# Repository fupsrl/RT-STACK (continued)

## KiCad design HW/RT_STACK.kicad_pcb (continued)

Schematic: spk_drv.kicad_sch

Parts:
C55: 100nF; C_0402_1005Metric
C56, C57: 220nF; C_0402_1005Metric
D25, D26, D27, D28: SK520B; D_SMB; LCSC C139681
Q19, Q20: RGPR30BM40; TO-252-2
R67, R68, R69, R70: 10; R_0402_1005Metric
U34: TC4427xOA; SOIC-8_3.9x4.9mm_P1.27mm; JLC C640788

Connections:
+5V: C55.1, U34.6 (VDD); also elsewhere on the board
+BATT: D25.1 (K), D27.1 (K); also elsewhere on the board
GND: C55.2, D26.2 (A), D28.2 (A), Q19.3 (E), Q20.3 (E), R69.1, R70.1, U34.3 (GND); also elsewhere on the board
IGN1: U34.2 (IN_A); also elsewhere on the board
IGN2: U34.4 (IN_B); also elsewhere on the board
unnamed: C56.2, R69.2
unnamed: C57.2, R70.2
unnamed: Q19.1 (G), R67.1
unnamed: Q20.1 (G), R68.1
unnamed: R67.2, U34.7 (OUT_A)
unnamed: R68.2, U34.5 (OUT_B)
SPK1: C57.1, D27.2 (A), D28.1 (K), Q20.2 (C); also elsewhere on the board
SPK2: C56.1, D25.2 (A), D26.1 (K), Q19.2 (C); also elsewhere on the board

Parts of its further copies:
C58, C61, C64, C67, C70: 100nF; C_0402_1005Metric
C59, C60, C62, C63, C65, C66, C68, C69, C71, C72: 220nF; C_0402_1005Metric
D29, D30, D31, D32, D33, D34, D35, D36, D37, D38, D39, D40, D41, D42, D43, D44, D45, D46, D47, D48: SK520B; D_SMB; LCSC C139681
Q21, Q22, Q23, Q24, Q25, Q26, Q27, Q28, Q29, Q30: RGPR30BM40; TO-252-2
R71, R72, R73, R74, R75, R76, R77, R78, R79, R80, R81, R82, R83, R84, R85, R86, R87, R88, R89, R90: 10; R_0402_1005Metric
U35, U36, U37, U38, U39: TC4427xOA; SOIC-8_3.9x4.9mm_P1.27mm; JLC C640788

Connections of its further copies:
+5V: C58.1, C61.1, C64.1, C67.1, C70.1, U35.6 (VDD), U36.6 (VDD), U37.6 (VDD), U38.6 (VDD), U39.6 (VDD); also elsewhere on the board
+BATT: D29.1 (K), D31.1 (K), D33.1 (K), D35.1 (K), D37.1 (K), D39.1 (K), D41.1 (K), D43.1 (K), D45.1 (K), D47.1 (K); also elsewhere on the board
GND: C58.2, C61.2, C64.2, C67.2, C70.2, D30.2 (A), D32.2 (A), D34.2 (A), D36.2 (A), D38.2 (A), D40.2 (A), D42.2 (A), D44.2 (A), D46.2 (A), D48.2 (A), Q21.3 (E), Q22.3 (E), Q23.3 (E), Q24.3 (E), Q25.3 (E), Q26.3 (E), Q27.3 (E), Q28.3 (E), Q29.3 (E), Q30.3 (E), R73.1, R74.1, R77.1, R78.1, R81.1, R82.1, R85.1, R86.1, R89.1, R90.1, U35.3 (GND), U36.3 (GND), U37.3 (GND), U38.3 (GND), U39.3 (GND); also elsewhere on the board
IGN3: U35.2 (IN_A); also elsewhere on the board
IGN4: U35.4 (IN_B); also elsewhere on the board
IGN5: U36.2 (IN_A); also elsewhere on the board
IGN6: U36.4 (IN_B); also elsewhere on the board
IGN7: U37.2 (IN_A); also elsewhere on the board
IGN8: U37.4 (IN_B); also elsewhere on the board
IGN9: U38.2 (IN_A); also elsewhere on the board
IGN10: U38.4 (IN_B); also elsewhere on the board
IGN11: U39.2 (IN_A); also elsewhere on the board
IGN12: U39.4 (IN_B); also elsewhere on the board
unnamed: C59.2, R73.2
unnamed: C60.2, R74.2
unnamed: C62.2, R77.2
unnamed: C63.2, R78.2
unnamed: C65.2, R81.2
unnamed: C66.2, R82.2
unnamed: C68.2, R85.2
unnamed: C69.2, R86.2
unnamed: C71.2, R89.2
unnamed: C72.2, R90.2
unnamed: Q21.1 (G), R71.1
unnamed: Q22.1 (G), R72.1
unnamed: Q23.1 (G), R75.1
unnamed: Q24.1 (G), R76.1
unnamed: Q25.1 (G), R79.1
unnamed: Q26.1 (G), R80.1
unnamed: Q27.1 (G), R83.1
unnamed: Q28.1 (G), R84.1
unnamed: Q29.1 (G), R87.1
unnamed: Q30.1 (G), R88.1
unnamed: R71.2, U35.7 (OUT_A)
unnamed: R72.2, U35.5 (OUT_B)
unnamed: R75.2, U36.7 (OUT_A)
unnamed: R76.2, U36.5 (OUT_B)
unnamed: R79.2, U37.7 (OUT_A)
unnamed: R80.2, U37.5 (OUT_B)
unnamed: R83.2, U38.7 (OUT_A)
unnamed: R84.2, U38.5 (OUT_B)
unnamed: R87.2, U39.7 (OUT_A)
unnamed: R88.2, U39.5 (OUT_B)
SPK3: C60.1, D31.2 (A), D32.1 (K), Q22.2 (C); also elsewhere on the board
SPK4: C59.1, D29.2 (A), D30.1 (K), Q21.2 (C); also elsewhere on the board
SPK5: C63.1, D35.2 (A), D36.1 (K), Q24.2 (C); also elsewhere on the board
SPK6: C62.1, D33.2 (A), D34.1 (K), Q23.2 (C); also elsewhere on the board
SPK7: C66.1, D39.2 (A), D40.1 (K), Q26.2 (C); also elsewhere on the board
SPK8: C65.1, D37.2 (A), D38.1 (K), Q25.2 (C); also elsewhere on the board
SPK9: C69.1, D43.2 (A), D44.1 (K), Q28.2 (C); also elsewhere on the board
SPK10: C68.1, D41.2 (A), D42.1 (K), Q27.2 (C); also elsewhere on the board
SPK11: C72.1, D47.2 (A), D48.1 (K), Q30.2 (C); also elsewhere on the board
SPK12: C71.1, D45.2 (A), D46.1 (K), Q29.2 (C); also elsewhere on the board

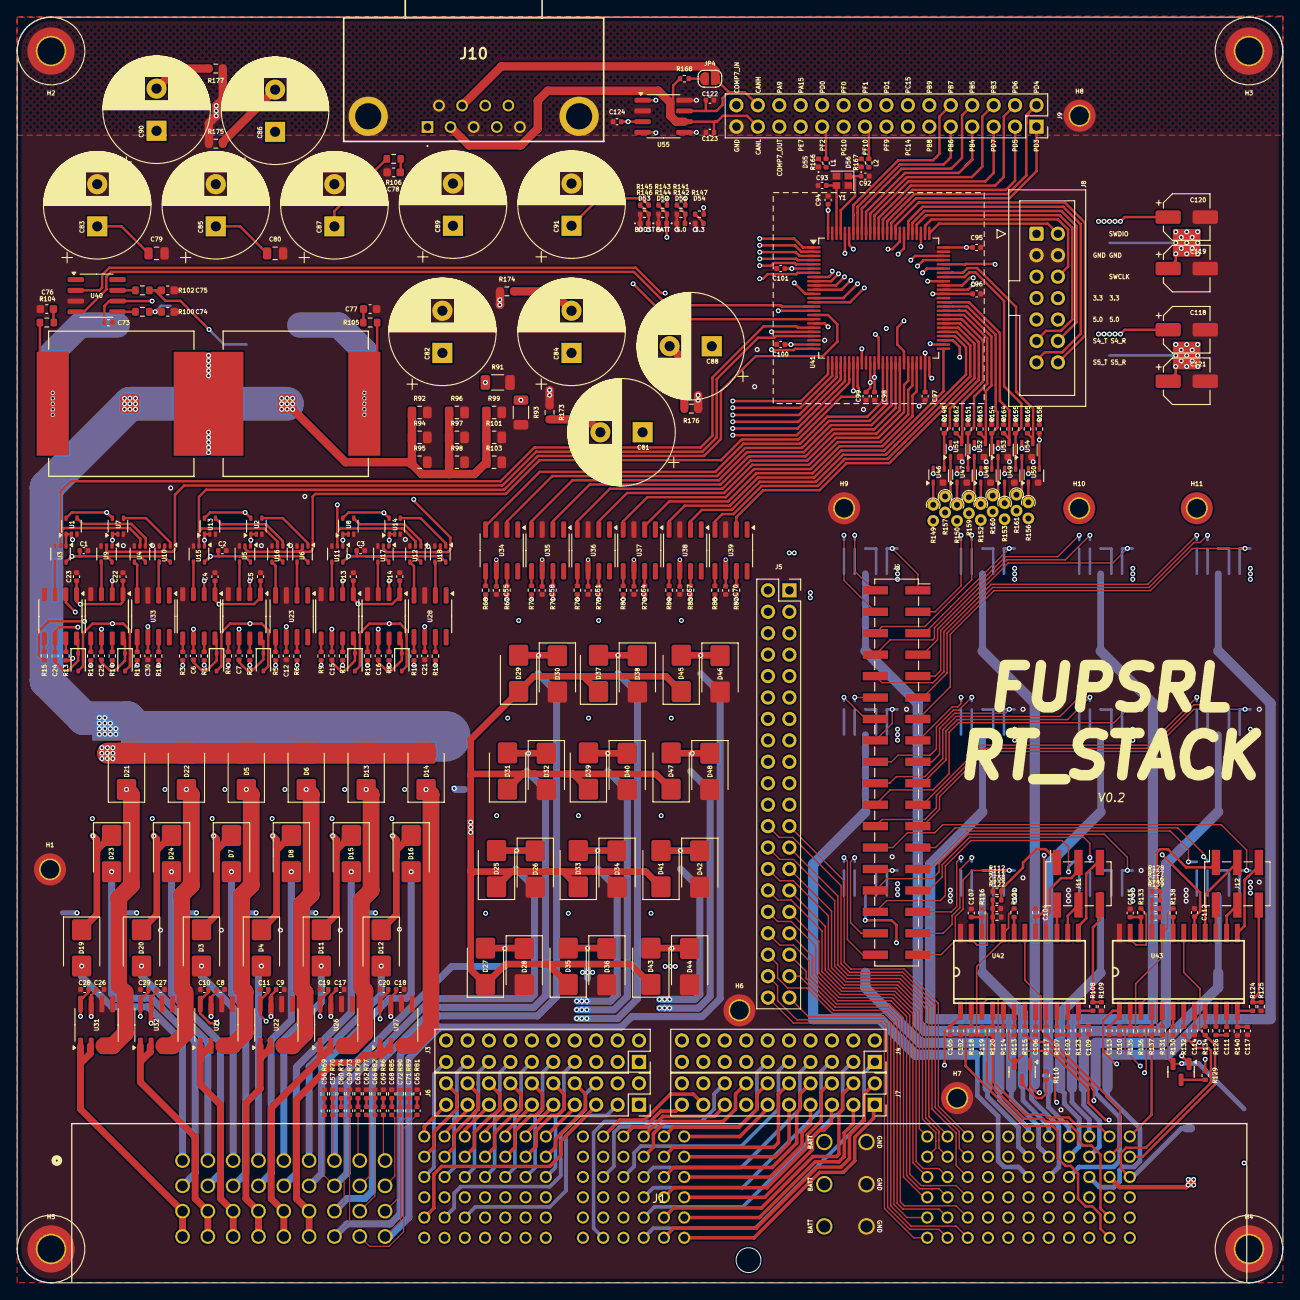
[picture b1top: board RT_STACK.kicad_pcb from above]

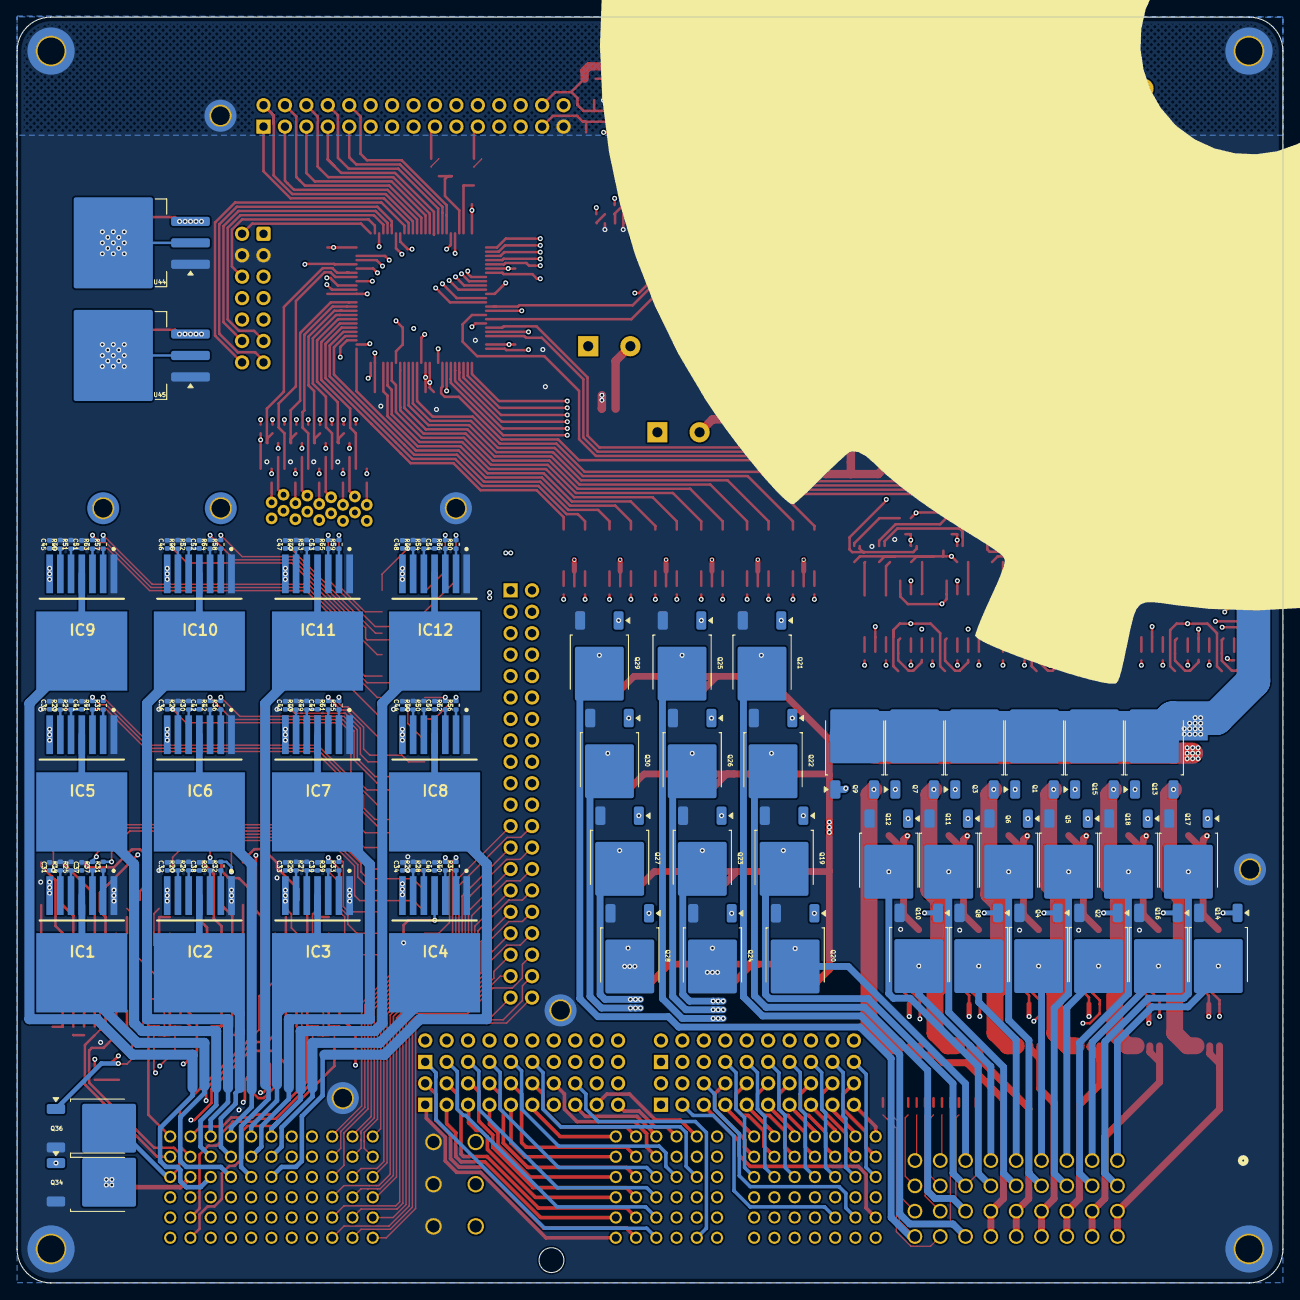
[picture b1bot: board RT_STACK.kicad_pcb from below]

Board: 6 copper layers, 150.0 x 150.0 mm, 483 parts (122 on the bottom side), 498 nets.

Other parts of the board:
C122, C123: 47p; C_0402_1005Metric
C124: 100n; C_0402_1005Metric
JP4: Jumper_2_Open; SolderJumper-2_P1.3mm_Open_RoundedPad1.0x1.5mm
R168: 60; R_0402_1005Metric
U55: TJA1051T-3; SOIC-8_3.9x4.9mm_P1.27mm

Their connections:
+3.3V: U55.5 (VIO); also elsewhere on the board
+5V: C124.2, U55.3 (VCC); also elsewhere on the board
/MCU/CAN_RX: U55.4 (RXD); also elsewhere on the board
/MCU/CAN_TX: U55.1 (TXD); also elsewhere on the board
CAN1_H: C122.1, JP4.2 (B), U55.7 (CANH); also elsewhere on the board
CAN1_L: C123.2, R168.1, U55.6 (CANL); also elsewhere on the board
GND: C122.2, C123.1, C124.1, U55.2 (GND), U55.8 (S); also elsewhere on the board
unnamed: JP4.1 (A), R168.2

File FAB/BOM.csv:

Id,Riferimento,Impronta,Quantità,Valore,JLCPCB Part #（optional）
2,"R164,R165,R148,R162,R144,R109,R125,R151,R146,R163,R155,R154,R112,R128,R158,R48,R21,R47,R23,R24,R44,R43,R45,R20,R19,R46,R22",R_0402_1005Metric,27,1k,C106235
8,"R139,R118,R133,R122,R135,R131,R114,R116,R140,R123",R_0402_1005Metric,10,100k,C481918
4,"R73,R71,R72,R67,R86,R81,R90,R83,R70,R79,R84,R82,R78,R68,R87,R80,R76,R69,R88,R77,R85,R89,R75,R74",R_0402_1005Metric,24,10,C137925
11,R168,R_0402_1005Metric,1,60,C137954
13,"R115,R132",R_0402_1005Metric,2,6.8k,C137847
17,"R13,R7,R2,R14,R1,R8",R_0402_1005Metric,6,R0,C106231
19,"R129,R110",R_0402_1005Metric,2,15,C138052
25,"R18,R15,R9,R11,R16,R3,R10,R5,R17,R12,R6,R4",R_0402_1005Metric,12,R10,C138052
26,"R117,R134",R_0402_1005Metric,2,301R,C477711
28,"R113,R130",R_0402_1005Metric,2,100,C106232
31,"R143,R141,R142",R_0402_1005Metric,3,5k,C477765
36,"R121,R138",R_0402_1005Metric,2,4.7k,C105871
38,"R167,R147,R166",R_0402_1005Metric,3,200,C114764
42,"R136,R119",R_0402_1005Metric,2,470k,C137976
45,"R127,R124,R108,R111",R_0402_1005Metric,4,600,C5120110
46,"R137,R120",R_0402_1005Metric,2,61.9R,C137953
49,"R107,R126",R_0402_1005Metric,2,31.6K,C276265
52,R145,R_0402_1005Metric,1,25k,C138027
68,"R30,R27,R25,R50,R53,R29,R49,R51,R52,R28,R54,R26",R_0402_1005Metric,12,0.51k,C276273
70,"R58,R32,R62,R59,R39,R65,R64,R56,R38,R61,R66,R37,R34,R40,R63,R31,R57,R33,R41,R42,R55,R60,R36,R35",R_0402_1005Metric,24,10k,C60489
57,"R102,R100",R_0603_1608Metric,2,10,
18,"R177,R175,R105,R173,R176,R174,R106,R104",R_0603_1608Metric,8,5.1,
30,"R95,R99,R92,R103,R101,R97,R94,R98,R96",R_0805_2012Metric,9,56k,
32,"R91,R93",R_1206_3216Metric,2,2K,
22,"R149,R150,R161,R152,R156,R160,R153,R157,R159",R_Axial_DIN0204_L3.6mm_D1.6mm_P1.90mm_Vertical,9,1k,
3,"C103,C64,C115,C22,C116,C11,C30,C2,C61,C73,C55,C21,C70,C5,C3,C12,C108,C109,C107,C20,C23,C1,C67,C19,C111,C13,C10,C58,C14,C4,C28,C117,C29,C42,C39,C53,C37,C41,C40,C38,C52,C49,C54,C50,C51",C_0402_1005Metric,45,100nF,
16,"C101,C94,C99,C96,C97,C95,C98,C100",C_0402_1005Metric,8,100nf,
20,"C7,C104,C105,C15,C112,C113,C25,C6,C24,C16",C_0402_1005Metric,10,1uF,
21,"C63,C60,C66,C69,C68,C57,C65,C59,C72,C56,C62,C71",C_0402_1005Metric,12,220nF,
23,"C85,C84,C83,C81,C82,C86,C90,C87,C88,C91,C89",CP_Radial_D12.5mm_P5.00mm,11,330uF,
27,"C74,C75",C_0603_1608Metric,2,470p,
29,"C27,C18,C9,C8,C26,C17",C_0402_1005Metric,6,10nF,
33,"C118,C121,C120,C119",CP_Elec_5x4.5,4,10uF,
35,"C77,C76,C78",C_0603_1608Metric,3,330p,
37,"C79,C80",C_0805_2012Metric,2,0.22uF,
39,C124,C_0402_1005Metric,1,100n,
40,"C102,C110",C_0402_1005Metric,2,2.2nF,
43,"C123,C122",C_0402_1005Metric,2,47p,
51,"C93,C92",C_0402_1005Metric,2,15pF,
54,"C114,C106,C45,C44,C31,C35,C33,C43,C34,C47,C46,C48,C36,C32",C_0402_1005Metric,14,1nF,
6,"D7,D36,D39,D46,D35,D15,D27,D34,D25,D38,D3,D48,D19,D31,D20,D23,D28,D13,D24,D44,D45,D40,D14,D12,D16,D30,D5,D43,D47,D32,D26,D22,D6,D21,D4,D8,D37,D29,D41,D11,D33,D42",D_SMB,42,SK520B,
14,"D53,D55,D54,D52,D51,D56",LED_0402_1005Metric,6,LED,
34,"D17,D18,D10,D1,D9,D2",D_SOD-323,6,1N4148WS,
69,"D50,D49",TO-263-2,2,STTH802G-TR,
7,"U4,U15,U17,U18,U9,U5,U6,U16,U12,U3,U10,U11",SOT-353_SC-70-5,12,SN74AHC1G08DCKR,
5,"U47,U52,U50,U46,U51,U48,U49,U53,U54",Analog_KS-4,9,ADCMP354,
1,"U8,U7,U2,U14,U13,U1",SOT-353_SC-70-5,6,SN74AHC1G02DCKR,
10,"U40,U39,U36,U37,U38,U33,U23,U35,U34,U28",SOIC-8_3.9x4.9mm_P1.27mm,10,TC4427xOA,
15,"U24,U30,U19,U25,U20,U29",SOIC-8_3.9x4.9mm_P1.27mm,6,IR2101,
47,"U22,U26,U31,U27,U21,U32",SOIC-8_3.9x4.9mm_P1.27mm,6,ACS722xLCTR-20AB,
48,"U43,U42",SO24W,2,CJ125,
55,U41,LQFP-100_14x14mm_P0.5mm,1,STM32G474VETx,
59,U55,SOIC-8_3.9x4.9mm_P1.27mm,1,TJA1051T-3,
71,U45,TO-263-3_TabPin2,1,LM1084-3.3,
72,U44,TO-263-3_TabPin2,1,LM1084-5.0,
9,"L1,L2",L_Vishay_IHLP-6767,2,10uH,
12,"J6,J4,J7,J3",PinSocket_2x10_P2.54mm_Vertical,4,Conn_02x10_Odd_Even,
24,"J12,J11",PinSocket_2x03_P2.54mm_Vertical_SMD,2,Conn_02x03_Odd_Even,
44,JP4,SolderJumper-2_P1.3mm_Open_RoundedPad1.0x1.5mm,1,Jumper_2_Open,
50,J2,PinSocket_2x18_P2.54mm_Vertical_SMD,1,Conn_02x18_Odd_Even,
53,J10,LD09S13A4GX00LF,1,LD09S13A4GX00LF,
56,J1,CONN_5601380001-SD_MOL,1,5601381861,
58,J5,PinSocket_2x20_P2.54mm_Vertical,1,Conn_02x20_Odd_Even,
60,J8,IDC-Header_2x07_P2.54mm_Vertical,1,Conn_02x07_Odd_Even,
62,J9,PinSocket_2x15_P2.54mm_Vertical,1,Conn_02x15_Odd_Even,
63,"Q17,Q12,Q7,Q1,Q15,Q2,Q18,Q4,Q16,Q10,Q9,Q11,Q3,Q14,Q13,Q6,Q8,Q5",TO-252-2,18,SUD80460E,
64,"Q31,Q32",TO-252-2,2,BUK9230-100B,
66,"Q27,Q19,Q28,Q22,Q25,Q20,Q21,Q29,Q30,Q26,Q23,Q24",TO-252-2,12,RGPR30BM40,
67,"Q36,Q34",TO-252-2,2,STD30NF06LT4,
41,"Q35,Q33",Q_SOT-23,2,SS8550,
61,Y1,Crystal_SMD_2016-4Pin_2.0x1.6mm,1,Crystal_GND24,
65,"IC7,IC9,IC4,IC11,IC2,IC6,IC12,IC10,IC8,IC5,IC3,IC1",PG-TO263-7-1,12,IFX007TAUMA1,

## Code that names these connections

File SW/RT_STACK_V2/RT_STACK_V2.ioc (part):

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Mcu.Name=STM32G474V(B-C-E)Tx
Mcu.Package=LQFP100
Mcu.UserName=STM32G474VETx
PA0.Mode=ExternalOutput
PA0.Signal=COMP1_OUT
PA1.Signal=SharedAnalog_PA1
PA10.GPIOParameters=GPIO_Label
PA10.GPIO_Label=TMG_OUT5
PA10.Signal=GPIO_Input
PA11.Mode=FDCAN_Activate
PA11.Signal=FDCAN1_RX
PA12.Mode=FDCAN_Activate
PA12.Signal=FDCAN1_TX
PA2.Mode=ExternalOutput
PA2.Signal=COMP2_OUT
PA3.Signal=SharedAnalog_PA3
PA4.GPIOParameters=GPIO_Label
PA4.GPIO_Label=BOOST910
PA4.Signal=GPIO_Output
PA5.GPIOParameters=GPIO_Label
PA5.GPIO_Label=BOOST1112
PA5.Signal=GPIO_Output
PA6.GPIOParameters=GPIO_Label
PA6.GPIO_Label=BOOST78
PA6.Signal=GPIO_Output
PA7.GPIOParameters=GPIO_Label
PA7.GPIO_Label=BOOST56
PA7.Signal=GPIO_Output
PA8.GPIOParameters=GPIO_Label
PA8.GPIO_Label=TMG_OUT9
PA8.Signal=GPIO_Input
PB0.Signal=SharedAnalog_PB0
PB1.Mode=ExternalOutput
PB1.Signal=COMP4_OUT
PB10.GPIOParameters=GPIO_Label
PB10.GPIO_Label=IGN7
PB10.Signal=GPIO_Output
PB11.Signal=SharedAnalog_PB11
PB12.GPIOParameters=GPIO_Label
PB12.GPIO_Label=IGN10
PB12.Signal=GPIO_Output
PB13.Signal=SharedAnalog_PB13
PB14.Mode=INP
PB14.Signal=COMP7_INP
PB15.GPIOParameters=GPIO_Label
PB15.GPIO_Label=IGN9
PB15.Signal=GPIO_Output
PB2.GPIOParameters=GPIO_Label
PB2.GPIO_Label=VBATT
PB2.Mode=IN12-Single-Ended
PB2.Signal=ADC2_IN12
PC0.Signal=S_TIM1_CH1
PC1.Signal=SharedAnalog_PC1
PC10.Mode=Asynchronous
PC10.Signal=UART4_TX
PC11.Mode=Asynchronous
PC11.Signal=UART4_RX
PC12.Mode=Asynchronous
PC12.Signal=UART5_TX
PC13.GPIOParameters=GPIO_Label
PC13.GPIO_Label=SEL910
PC13.Signal=GPIO_Output
PC2.Mode=ExternalOutput
PC2.Signal=COMP3_OUT
PC3.GPIOParameters=GPIO_Label
PC3.GPIO_Label=VBUS
PC3.Mode=IN9-Single-Ended
PC3.Signal=ADC1_IN9
PC4.GPIOParameters=GPIO_Label
PC4.GPIO_Label=BOOST34
PC4.Signal=GPIO_Output
PC5.GPIOParameters=GPIO_Label
PC5.GPIO_Label=BOOST12
PC5.Signal=GPIO_Output
PC6.Mode=ExternalOutput
PC6.Signal=COMP6_OUT
PC7.Mode=ExternalOutput
PC7.Signal=COMP5_OUT
PC8.Mode=ExternalOutput
PC8.Signal=COMP7_OUT
PC9.GPIOParameters=GPIO_Label
PC9.GPIO_Label=TMG_OUT3
PC9.Signal=GPIO_Input
PD10.GPIOParameters=GPIO_Label
PD10.GPIO_Label=TMG_OUT1
PD10.Signal=GPIO_Input
PD11.GPIOParameters=GPIO_Label
PD11.GPIO_Label=TMG_OUT6
PD11.Signal=GPIO_Input
PD12.GPIOParameters=GPIO_Label
PD12.GPIO_Label=TMG_OUT2
PD12.Signal=GPIO_Input
PD13.GPIOParameters=GPIO_Label
PD13.GPIO_Label=TMG_OUT7
PD13.Signal=GPIO_Input
PD14.GPIOParameters=GPIO_Label
PD14.GPIO_Label=TMG_OUT4
PD14.Signal=GPIO_Input
PD15.GPIOParameters=GPIO_Label
PD15.GPIO_Label=TMG_OUT8
PD15.Signal=GPIO_Input
PD2.Mode=Asynchronous
PD2.Signal=UART5_RX
PD8.GPIOParameters=GPIO_Label
PD8.GPIO_Label=IGN12
PD8.Signal=GPIO_Output
PD9.GPIOParameters=GPIO_Label
PD9.GPIO_Label=IGN11
PD9.Signal=GPIO_Output
PE10.GPIOParameters=GPIO_Label
PE10.GPIO_Label=IGN4
PE10.Signal=GPIO_Output
PE11.GPIOParameters=GPIO_Label
PE11.GPIO_Label=IGN3
PE11.Signal=GPIO_Output
PE12.GPIOParameters=GPIO_Label
PE12.GPIO_Label=IGN6
PE12.Signal=GPIO_Output
PE13.Signal=S_TIM1_CH3
PE14.GPIOParameters=GPIO_Label
PE14.GPIO_Label=IGN5
PE14.Signal=GPIO_Output
PE15.GPIOParameters=GPIO_Label
PE15.GPIO_Label=IGN8
PE15.Signal=GPIO_Output
PE2.GPIOParameters=GPIO_Label
PE2.GPIO_Label=SEL12
PE2.Signal=GPIO_Output
PE3.GPIOParameters=GPIO_Label
PE3.GPIO_Label=SEL34
PE3.Signal=GPIO_Output
PE4.GPIOParameters=GPIO_Label
PE4.GPIO_Label=SEL56
PE4.Signal=GPIO_Output
PE5.GPIOParameters=GPIO_Label
PE5.GPIO_Label=SEL78
PE5.Signal=GPIO_Output
PE6.GPIOParameters=GPIO_Label
PE6.GPIO_Label=SEL1112
PE6.Signal=GPIO_Output
PE8.GPIOParameters=GPIO_Label
PE8.GPIO_Label=IGN2
PE8.Signal=GPIO_Output
PE9.GPIOParameters=GPIO_Label
PE9.GPIO_Label=IGN1
PE9.Signal=GPIO_Output
PF0-OSC_IN.Mode=HSE-External-Oscillator
PF0-OSC_IN.Signal=RCC_OSC_IN
PF1-OSC_OUT.Mode=HSE-External-Oscillator
PF1-OSC_OUT.Signal=RCC_OSC_OUT
PF10.GPIOParameters=GPIO_Label
PF10.GPIO_Label=LED2
PF10.Signal=GPIO_Output
PF2.GPIOParameters=GPIO_Label
PF2.GPIO_Label=LED1
PF2.Signal=GPIO_Output
RCC.HSE_VALUE=20000000
RCC.SYSCLKFreq_VALUE=170000000
RCC.SYSCLKSource=RCC_SYSCLKSOURCE_PLLCLK
board=custom

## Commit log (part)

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2026-01-05 Alpha release
2026-01-05 Alpha release
    First manifactured release
2026-01-05 License
2026-03-08 Ver2
    Second HW rev + SW update
2026-03-09 v0.2 BOM
2026-04-05 FAB BOM/CPL
    add BOM/CPL JLCPCB reduced (only stm32/0402 components)
2026-06-27 Firmware
    Trigger wheels pattern detections
    Ignition scheduler
    Injection schedurer
    GDI support
